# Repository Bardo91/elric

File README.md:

OpenSource Robotic arm - making a dream become true

# CAD Design

# Prototype

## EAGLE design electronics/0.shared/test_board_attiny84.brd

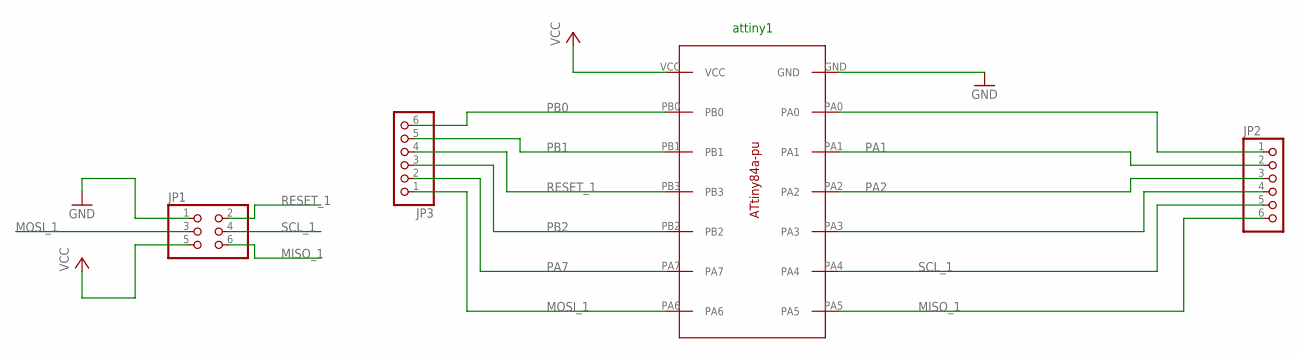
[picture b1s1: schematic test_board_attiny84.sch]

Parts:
JP1: PINHD-2X3; 2X03
JP2, JP3: PINHD-1X6; 1X06
U$8: ATTINY84A-PU

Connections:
GND: JP1.1, U$8.GND
MISO_1: JP1.6, JP2.6, U$8.PA5
MOSI_1: JP1.3, JP3.1, U$8.PA6
unnamed: JP2.1, U$8.PA0
PA1: JP2.2, U$8.PA1
PA2: JP2.3, U$8.PA2
PA3: JP2.4, U$8.PA3
PA7: JP3.2, U$8.PA7
PB0: JP3.6, U$8.PB0
PB1: JP3.5, U$8.PB1
PB2: JP3.3, U$8.PB2
RESET_1: JP1.2, JP3.4, U$8.PB3
SCL_1: JP1.4, JP2.5, U$8.PA4
VCC: JP1.5, U$8.VCC

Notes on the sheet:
attiny1

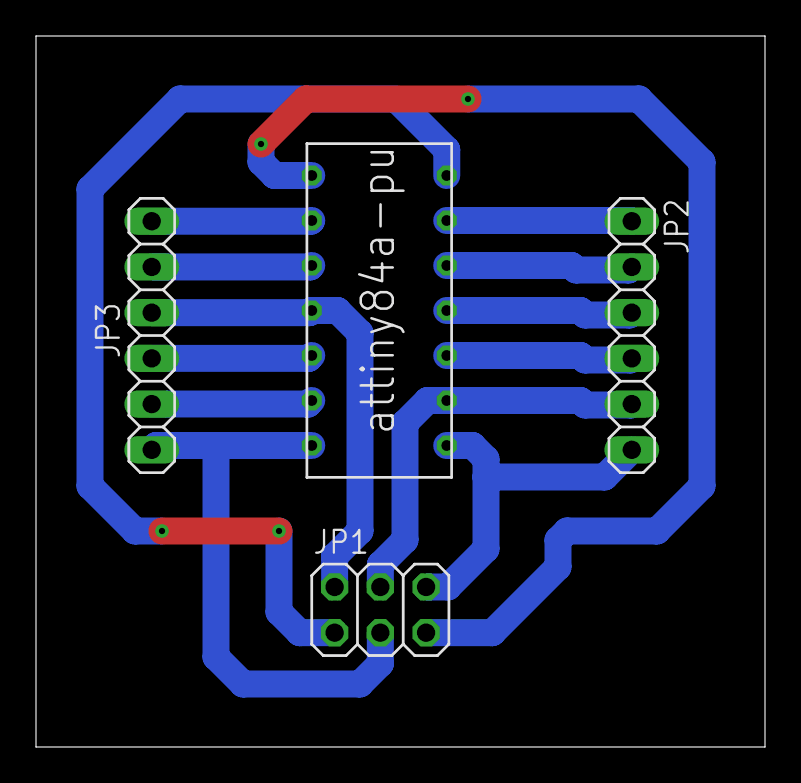
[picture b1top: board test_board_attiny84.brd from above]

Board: 2 copper layers, 40.5 x 39.5 mm, 4 parts (0 on the bottom side), 14 nets.

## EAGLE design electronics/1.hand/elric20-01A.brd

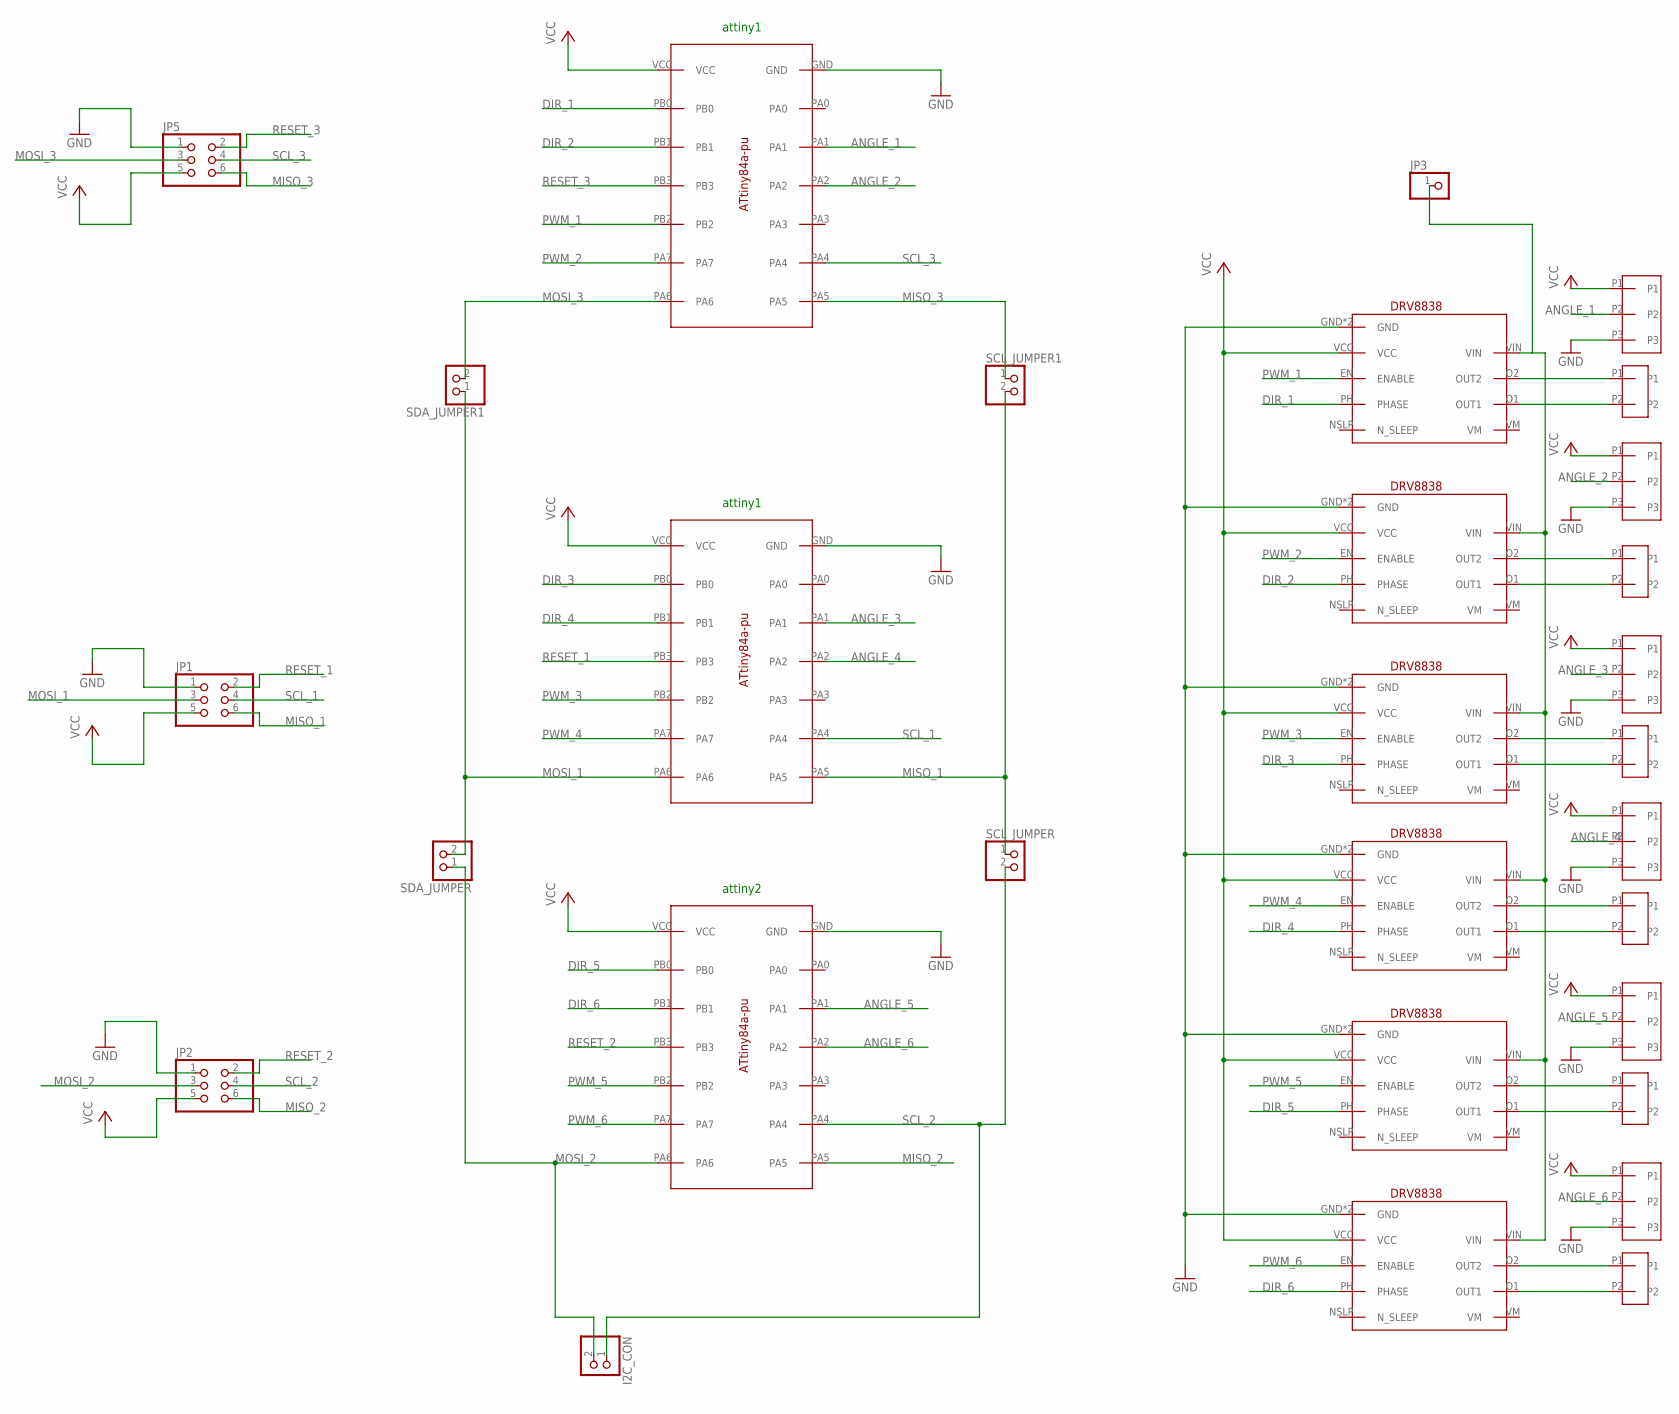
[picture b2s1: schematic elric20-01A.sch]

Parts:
I2C_CON: PINHD-1X2; 1X02
JP1, JP2, JP5: PINHD-2X3; 2X03
JP3: PINHD-1X1; 1X01
SCL_JUMPER, SCL_JUMPER1: PINHD-1X2; 1X02
SDA_JUMPER, SDA_JUMPER1: PINHD-1X2; 1X02
U$1, U$8, U$21: ATTINY84A-PU
U$2, U$3, U$4, U$5, U$6, U$7: DRV8838
U$9, U$10, U$11, U$12, U$13, U$14: PAD_SMD_X2_BIG
U$15, U$16, U$17, U$18, U$19, U$20: PAD_SMD_X3

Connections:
ANGLE_1: U$20.P2, U$21.PA1
ANGLE_2: U$19.P2, U$21.PA2
ANGLE_3: U$8.PA1, U$18.P2
ANGLE_4: U$8.PA2, U$17.P2
ANGLE_5: U$1.PA1, U$16.P2
ANGLE_6: U$1.PA2, U$15.P2
DIR_1: U$2.PH (PHASE), U$21.PB0
DIR_2: U$3.PH (PHASE), U$21.PB1
DIR_3: U$4.PH (PHASE), U$8.PB0
DIR_4: U$5.PH (PHASE), U$8.PB1
DIR_5: U$1.PB0, U$6.PH (PHASE)
DIR_6: U$1.PB1, U$7.PH (PHASE)
GND: JP1.1, JP2.1, JP5.1, U$1.GND, U$2.GND, U$2.GND2 (GND), U$3.GND, U$3.GND2 (GND), U$4.GND, U$4.GND2 (GND), U$5.GND, U$5.GND2 (GND), U$6.GND, U$6.GND2 (GND), U$7.GND, U$7.GND2 (GND), U$8.GND, U$15.P3, U$16.P3, U$17.P3, U$18.P3, U$19.P3, U$20.P3, U$21.GND
MISO_1: JP1.6, SCL_JUMPER.1, SCL_JUMPER1.2, U$8.PA5
MISO_2: JP2.6, U$1.PA5
MISO_3: JP5.6, SCL_JUMPER1.1, U$21.PA5
MOSI_1: JP1.3, SDA_JUMPER.2, SDA_JUMPER1.1, U$8.PA6
MOSI_2: I2C_CON.2, JP2.3, SDA_JUMPER.1, U$1.PA6
MOSI_3: JP5.3, SDA_JUMPER1.2, U$21.PA6
unnamed: U$2.O2 (OUT2), U$9.P1
unnamed: U$2.O1 (OUT1), U$9.P2
unnamed: U$3.O2 (OUT2), U$10.P1
unnamed: U$3.O1 (OUT1), U$10.P2
unnamed: U$4.O2 (OUT2), U$11.P1
unnamed: U$4.O1 (OUT1), U$11.P2
unnamed: U$5.O2 (OUT2), U$12.P1
unnamed: U$5.O1 (OUT1), U$12.P2
unnamed: U$6.O2 (OUT2), U$13.P1
unnamed: U$6.O1 (OUT1), U$13.P2
unnamed: U$7.O2 (OUT2), U$14.P1
unnamed: U$7.O1 (OUT1), U$14.P2
unnamed: JP3.1, U$2.VIN, U$3.VIN, U$4.VIN, U$5.VIN, U$6.VIN, U$7.VIN
PWM_1: U$2.EN (ENABLE), U$21.PB2
PWM_2: U$3.EN (ENABLE), U$21.PA7
PWM_3: U$4.EN (ENABLE), U$8.PB2
PWM_4: U$5.EN (ENABLE), U$8.PA7
PWM_5: U$1.PB2, U$6.EN (ENABLE)
PWM_6: U$1.PA7, U$7.EN (ENABLE)
RESET_1: JP1.2, U$8.PB3
RESET_2: JP2.2, U$1.PB3
RESET_3: JP5.2, U$21.PB3
SCL_1: JP1.4, U$8.PA4
SCL_2: I2C_CON.1, JP2.4, SCL_JUMPER.2, U$1.PA4
SCL_3: JP5.4, U$21.PA4
VCC: JP1.5, JP2.5, JP5.5, U$1.VCC, U$2.VCC, U$3.VCC, U$4.VCC, U$5.VCC, U$6.VCC, U$7.VCC, U$8.VCC, U$15.P1, U$16.P1, U$17.P1, U$18.P1, U$19.P1, U$20.P1, U$21.VCC

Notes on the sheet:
attiny1
attiny2

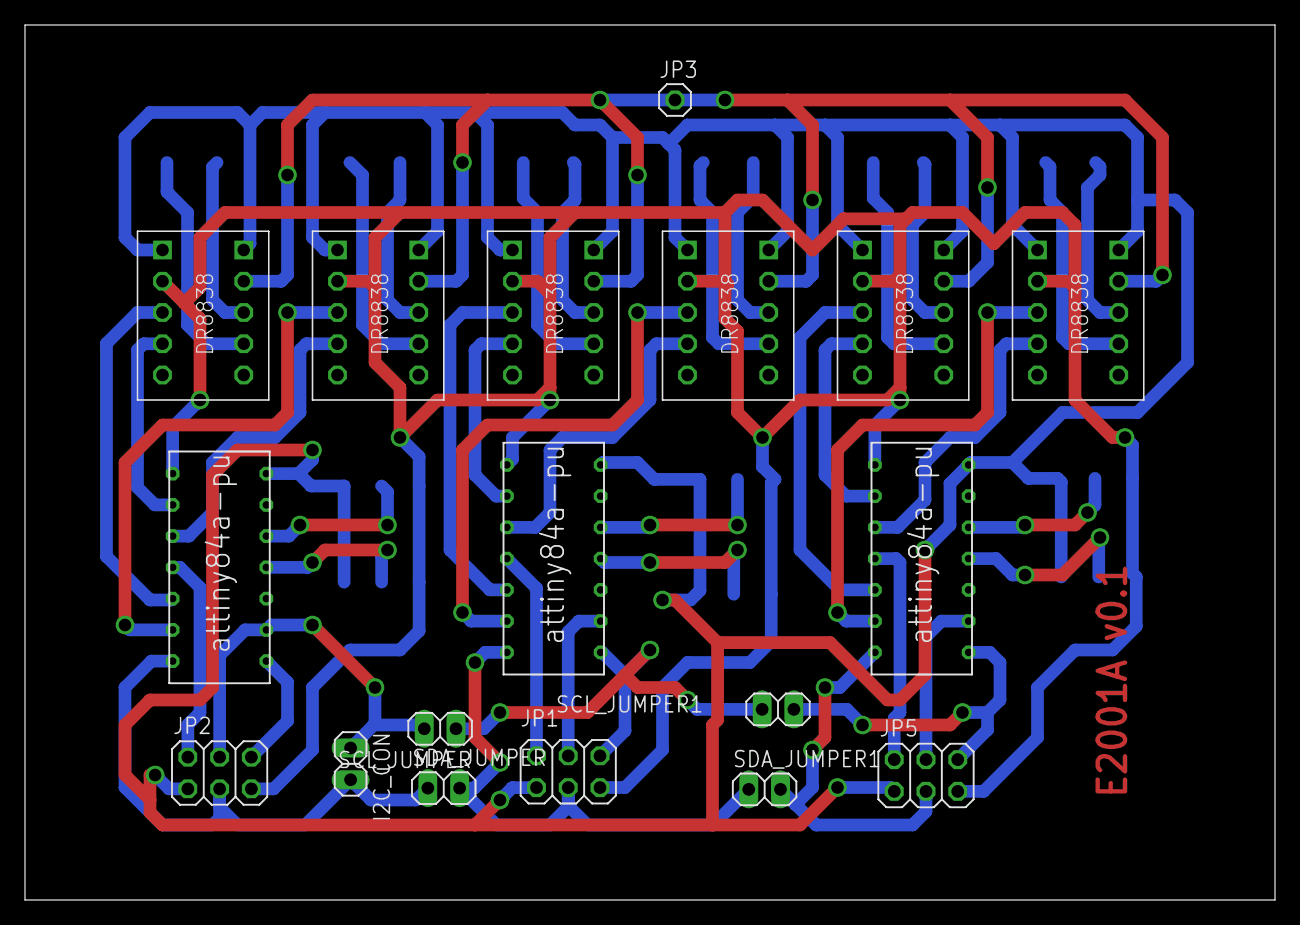
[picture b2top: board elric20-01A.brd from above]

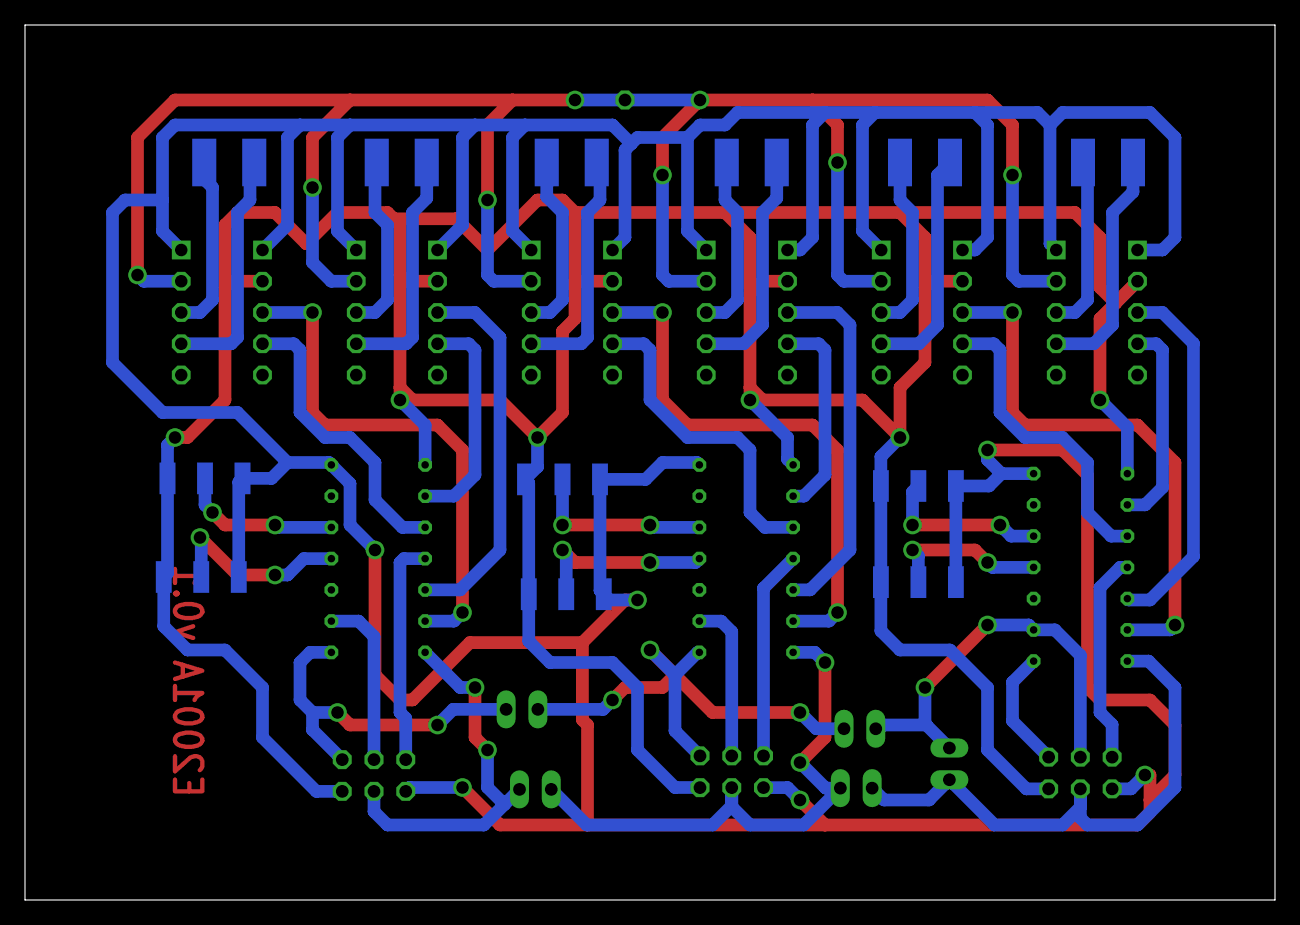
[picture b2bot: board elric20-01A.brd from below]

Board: 2 copper layers, 100.0 x 70.0 mm, 30 parts (12 on the bottom side), 45 nets.

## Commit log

2020-04-09 Init files
2020-04-09 pinky v2.0 working mechanism.
2020-04-10 Four fingers v2.0
2020-04-10 thumb and partial case
2020-04-11 Added 3rd case to hand and added logo
2020-04-11 dummy wrist joint
2020-04-11 minor changes in case
2020-04-12 Renamed folders and files according to new nomemclature
2020-04-12 Fixed hand motors holders. Case fixes. Added arm assembly.
2020-04-12 Renamed assemblies. Added forearm and forearm cases
2020-04-12 Fixes in arm_case
2020-04-12 first draft forearm. WIP: arm
2020-04-12 renamed project file
2020-04-13 Finish hand case attachment and minor fixes
2020-04-13 WIP: elbow engine
2020-04-13 First version elbow
2020-04-15 Arm finished with case and attachments
2020-04-16 case arm and forearm
2020-04-17 ribbed case foream 2
2020-04-18 Testing /coding minimal examples with attiny85
2020-04-18 Fixed register address, working library for gpio. next pwm!
2020-04-18 ups,
2020-04-18 working raw pwm test
2020-04-18 coded 8 bit timer
2020-04-18 renamed examples, added timer to attiny84, generalized examples.
2020-04-25 Printing new version of elbow to test joint.
2020-04-25 WIP: ADC
2020-04-25 WIP: debugging ADC
2020-04-25 working ADC
2020-04-25 working adc and pwm but OCR0A set value
2020-04-25 Fixed register set value. Working ADC and PWM
2020-04-26 Fixes in elbow related with dimensions of servo. Rework of motor_dc_6v_30rpm.ipt. Created test structure for PID software
2020-04-28 many things... I do not remember XD sorry
2020-05-02 Finally arranged files as library.
2020-05-02 WorkingPID
2020-05-09 Fixes in hand joint engines
2020-05-09 WIP elric20-01A electronics
2020-05-09 Updated potentiometer_holder.ipt so it can be flipped
2020-05-09 Elric20 images
2020-05-09 updated doc image
2020-05-10 First version hand electronics
2020-05-10 Added board name and version
2020-05-19 New version of hand electronics. Packed in servos 2 by 2
2020-05-28 Prepared system to compile in MVS
2020-05-29 Fixed cmake list for compilation in windows and unix
2020-05-31 Moved elric20-01A files to an old folder. Created elric20-01B. New finger design, but thumb.
2020-06-02 Fixes in base hand
2020-06-02 Added developer board for ATtiny84
